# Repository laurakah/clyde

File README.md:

# Clyde

Clyde is an indoor room mapping roboter.

He is able to explore rooms, measure them and recognize them.

Clyde returns a map of the surveyed room to his user.

A possible field of use for Clyde could be the investigation of wireless signal quality on different spots in one or more rooms.

       .---.           _....._
     /  p  `\     .-""`:     :`"-.
     |__   - |  ,'     .     '    ',
      ._>    \ /:      :     ;      :,
       '-.    '\`.     .     :     '  \
          `.   | .'._.' '._.' '._.'.  |
            `;-\.   :     :     '   '/,__,
            .-'`'._ '     .     : _.'.__.'
           ((((-'/ `";--..:..--;"` \
               .'   /           \   \
              ((((-'           ((((-'

## directory structure

project/	– project documentation

software/	– software components for the robot (plus develepment tools)

hardware/	- hardware components for the robot

## system design

## build status for simulator tests

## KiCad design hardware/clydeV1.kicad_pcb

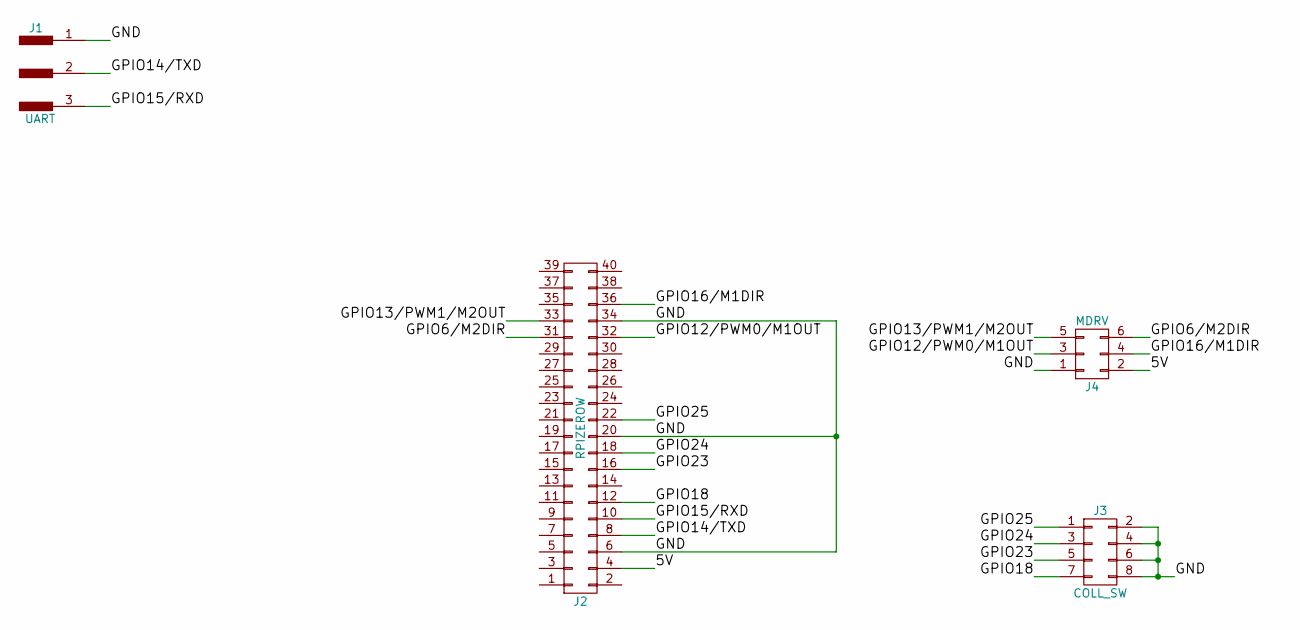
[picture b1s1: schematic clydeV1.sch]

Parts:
J1: UART; Pin_Header_Angled_1x03_Pitch2.54mm
J2: RPIZEROW; Socket_Strip_Straight_2x20_Pitch2.54mm
J3: COLL_SW; Pin_Header_Angled_2x04_Pitch2.54mm
J4: MDRV; Pin_Header_Angled_2x03_Pitch2.54mm

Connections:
/5V: J2.4, J4.2
/GND: J1.1, J2.6, J2.20, J2.34, J3.2, J3.4, J3.6, J3.8, J4.1
/GPIO6/M2DIR: J2.31, J4.6
/GPIO12/PWM0/M1OUT: J2.32, J4.3
/GPIO13/PWM1/M2OUT: J2.33, J4.5
/GPIO14/TXD: J1.2, J2.8
/GPIO15/RXD: J1.3, J2.10
/GPIO16/M1DIR: J2.36, J4.4
/GPIO18: J2.12, J3.7
/GPIO23: J2.16, J3.5
/GPIO24: J2.18, J3.3
/GPIO25: J2.22, J3.1

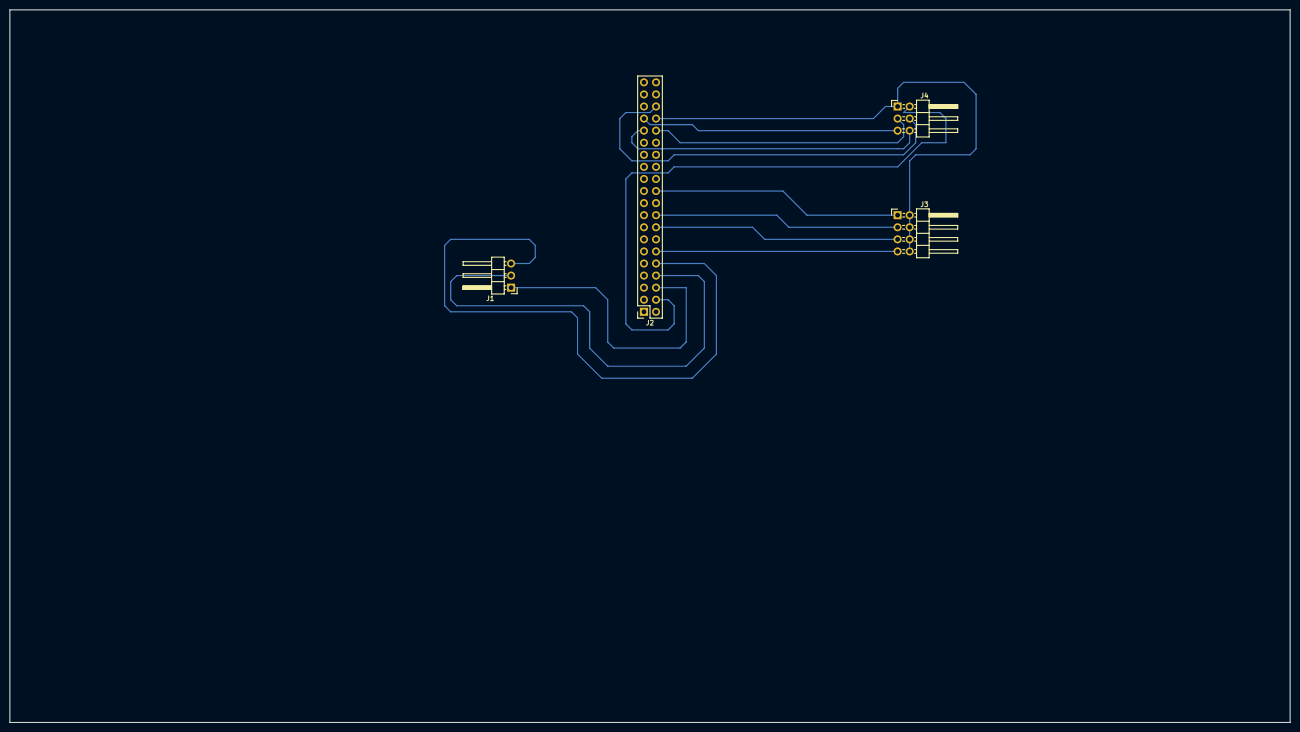
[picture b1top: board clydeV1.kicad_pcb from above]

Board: 2 copper layers, 269.2 x 149.9 mm, 4 parts (0 on the bottom side), 12 nets.

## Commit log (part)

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2017-07-16 update README.md - what is Clyde?
2017-07-16 add features.txt
2017-07-18 Components: Added links for sourcing components.
2017-07-18 Added images of our components.
2017-07-19 sim: Moved python code to sim directory.
2017-07-19 sim: Added Makefile to execute our tests.
2017-07-19 include build status for simulator tests in README.md
2017-07-19 SIM: add game map class + tests
2017-07-19 sim: Updated Makefile to execute gameMapTest.py as well.
2017-07-19 README: Use raw SVG for block diagram image.
2017-07-19 project: Generate .PNG output for block diagrams.
2017-07-19 README: Removed square braces not needed to display block diagram image.
2017-07-19 translate README.md and features.txt
2017-07-19 add features to README.md
2017-07-22 SIM: initial commit for simulator environment
2017-07-22 SIM: Added execution of simTest.py to Makefile.
2017-07-23 SIM: add time out and run wrapper + tests
2017-07-23 SIM: add baseRoomDetectionBrain + tests
2017-07-23 SIM: Added main.py to call simulator.
2017-07-23 SIM: Refactored main.py.
2017-07-23 SIM: add 4 new test maps
2017-07-23 SIM: Execute simulations for maps in order.
2017-07-23 SIM: WIP Added static method to GameMap to validate game map file lines.
2017-07-24 SIM: implement different exit codes for simulator
2017-07-24 SIM: Show exit code message in sim main() output.
2017-07-29 SIM: add collision detection on orientation up + tests
2017-07-29 SIM: clean up test code
2017-07-29 SIM: update player sim to give the right inputs and outputs to the brain sim
2017-07-29 SIM: exit with non-zero when sim execution failed.
2017-07-29 SIM: adjusted per-map result output format.
2017-07-30 SIM: add move function for player and player get position function
2017-07-30 SIM: Add function to return non-collision fields of a map.
2017-07-30 SIM: Added start position to report.
2017-07-30 SIM: Add more tests for getNonCollisionFields() to force our implementation to improve.
2017-07-30 SIM: add setPosition function for testing
2017-07-30 SIM: Added Sim.getStepDelay().
2017-07-30 SIM: Refactored Sim.step().
2017-07-30 SIM: Rename stepDelay to express the unit step delay represents (milliseconds).
2017-07-30 SIM: Pass delay to Sim in main.py. Updated usage/help.
2017-08-05 SIM: add getPlayerMap function in sim + tests
2017-08-05 SIM: add simMap and playerMap to report
2017-08-05 SIM: add random player start orientationon sim init
2017-08-06 SIM: normalize locations in game map array function + tests
2017-08-08 SIM: add follow function for player in draw function
2017-08-08 SIM: Add drawSimMap() with player position.
2017-08-08 SIM: Added new draw() that calls drawSimMap().
2017-08-08 SIM: Use class symbols for game map field values.
2017-08-10 SIM: clean up exceptions for base brain class
2017-08-10 SIM: add loadMapFile() to game map
2017-08-10 SIM: Add TODO and FIXME comments.
2017-08-12 SIM: Add code to draw() so sim and player map are displayed side by side.
2017-08-12 SIM: Made SimulatorLauncher test case class name reflect its purpose.
2017-08-12 SIM: Allow finding brain modules (via SimulatorLauncher).
2017-08-12 SIM: Rename method to get brain class names and change it to return class paths.
2017-08-12 SIM: Make main.py find brains on its own or allow passing one or more brains as arguments.
2017-08-12 SIM: implement movement functions in step function of brain
2017-08-12 SIM: check that arr is of type list for getLocationFromArray and setLocationInArray functions
2017-08-12 SIM: throw exceptions when index is out of range for getLocation and setLocation functions
2017-08-12 SIM: fix coordinate index in isCollision functions
2017-08-12 SIM: rename baseRoomDetectionBrain to baseBrain without deleting files
2017-08-12 SIM: prevent brain from moving as long as front collision is given
2017-08-12 SIM: Adjust output of sim.
2017-08-12 SIM: beautify draw game map tests
2017-08-12 SIM: Refactor Player.init slightly.
2017-08-12 SIM: Clean up Player.move().
2017-08-12 SIM: Added stub for DullBrain and its test case.
2017-08-12 SIM: Ignore DullBrain for execution with main.py
2017-08-12 SIM: Make Sim drawSimMap() and drawPlayerMap() draw player with orientation.
2017-08-12 SIM: Move loading class to main() of main.py.
2017-08-12 SIM: Have rv declared in main().
2017-08-12 SIM: Add comments to launchSim().
2017-08-13 SIM: make getSimMap() and getPlayerMap() return a gameMap object instead of an array
2017-08-13 SIM: Move parts of sim init into new reset() func.
2017-08-13 SIM: Refactor sim.init() into smaller parts.
2017-08-13 SIM: have dullBrain for testing purposes
2017-08-13 SIM: give simulator player.getOrientation() method
2017-08-13 SIM: give theaseus brain isFinished() method
2017-08-16 SIM: check that brain has map with start location and appends map according to orientation
2017-08-16 SIM: append brain map with collision and non collision fields for front collision
2017-08-16 SIM: Make launchSim() return dict (that is goint to be the report).
2017-08-16 SIM: Fixup for 2d375c3 - forgot to change order of arguments when calling launchSim).
2017-08-20 HARDWARE: add kicat project for circuit board
2017-08-20 SIM: rename game map objects from m to mObj
2017-08-20 SIM: give game map writeMapFile()
2017-08-20 SIM: Make launchSimForAllMaps() ignore maps passed using excludeMaps list argument.
2017-08-20 SIM: Verify launchSimForAllMaps() passes brainClassPath to launchSim().
2017-08-20 SIM: Verify launchSimForAllMaps() passes path to gameMapFile to launchSim().
2017-08-20 SIM: Verify timeout gets passed from launchSimForAllMaps() to launchSim().
2017-08-20 SIM: Verify follow arg is passed from launchSimForAllMaps() to launchSim().
2017-08-20 SIM: Make fakeLaunchSim() more compact.
2017-08-20 SIM: Clean up launchSimForAllMaps() tests.
2017-08-22 SIM: store last orientation on collision
2017-08-22 SIM: add getNextOrientation(), fixes #15
2017-08-22 SIM: refactor getNextOrientation()
2017-08-22 SIM: Replace launchSimForAllMaps() with TDD version from simLauncher.
2017-08-23 SIM: Replaced call to player.getOrientation() with self.getOrientation() in sim.
2017-08-23 SIM: replace orientation value with global brain symbols
2017-08-23 SIM: Make GameMap.arrayToText() optionally pad short lines of text maps.
2017-08-23 SIM: clean up comments
2017-08-26 SIM: Added comments to step() inside theseus brain.
2017-08-26 SIM: Move getting location value inside theseusBrain.step() to one place.
2017-08-26 SIM: add function to expand game map vertically
2017-08-26 SIM: add expandGameMap function, fixes #10
2017-08-26 SIM: refactor player move() to call getNextPosition()
2017-08-27 SIM: expand step function to prepend map on orientation down and left
2017-08-27 SIM: make sure getNextPosition is only called when no collision
2017-08-27 SIM: remove debugging code
2017-08-27 SIM: translate unknown fields into ? in string, fixes #20
2017-08-27 SIM: FIX: make sure y prepend operations expand x too
2017-08-27 SIM: Make maps be executed in order. fixes #18.
2017-08-27 SIM: raise exception when None is passed to getNextPosition(), fixes #23
2017-08-27 SIM: move update map stuff to own function
2017-08-27 SIM: Slightly refactor launchSim() in main.py so we can replace it without losing status output features.
2017-08-27 SIM: refactor updateMap()
2017-08-27 SIM: FIX: only increment position on orientation left and down when not prepending
2017-08-27 SIM: FIX: make withinMap() return false when called with zero
2017-08-30 SIM: refactor coordinates everywhere to use Coordinate class
2017-08-30 SIM: rename simple brain class
2017-09-02 SIM: Use new Coordinate object in main.py.
2017-09-02 SIM: add getLastPosition()
2017-09-02 SIM: add step log for brains
2017-09-03 SIM: add function to set up mocks and refactor tests for simple brain
2017-09-03 SIM: refactor last two functions in simple brain to use fake mocks
2017-09-03 SIM: Make launchSimForAllMaps() pass 'position' string to launchSim().
2017-09-03 SIM: Make launchSimForAllMaps() pass 'orientation' string to launchSim().
2017-09-03 SIM: make sure, getBrainMap() from baseBrain returns copy
2017-09-03 SIM: Fixup for passing position and orientation (but now in actual main.py).
2017-09-03 SIM: Added todo comments to simLauncherTest.
2017-09-03 SIM: Handle KeyboardInterrupt in main.py, fixes #22
2017-09-03 SIM: remove FIXME for getNonCollisionFields()
2017-09-03 SIM: remove pos, ori and direction from move helper function
2017-09-03 SIM: Added sparator comments between Sim unit tests.
2017-09-06 SIM: use fake values in every player isFinished test
2017-09-06 SIM: Fixed typo in comment.
2017-09-06 SIM: Simplify actual padding of map text.
2017-09-06 SIM: revert changes on test for player isFinished()
2017-09-06 SIM: Have GameMap.toText() that calls static arrayToText().
2017-09-06 SIM: Use GameMap.toText() where there is very low chance of breaking something.
2017-09-06 SIM: Have test that Sim.drawSimMap() calls toText() with pad=True.
2017-09-06 SIM: Removed outdated fixme comment.
2017-09-06 SIM: Adjusted test name for where we test Sim.draw() passes pad=True to toText().
2017-09-06 SIM: Fix malfunctioning sim.draw() where player map not properly displayed.
    The problem was that the player map (on the right side), actually the last
    line of the map, was moved towards the left into the sim map. This was because
    we used rstrip() on the text of the sim map (with the intention of removing the
    last new-line character. But, we forgot to pass "\n" to rstrip, which in turn
    removed all the spaces that have been added by GameMap.toText(pad=True) before.
    Hence, padding was working but destroyed by Sim.draw().
2017-09-15 SIM: Added new static method to find map files in a directory.
2017-09-15 SIM: Adjusted launchSimForAllMaps() to use list of maps rather than map file directory.
2017-09-15 SIM: Make launchSimForAllMaps() no longer filter maps by startsWith string.
2017-09-15 SIM: Make sure brain and map dir are used when alternative paths are supplied as command-line arguments.
2017-09-15 SIM: Have launchSimForAllBrains().
2017-09-15 SIM: Slightly simplify validity checking of position and orientation in simLauncher.
2017-09-15 SIM: Add array of orientation strings to base brain.
2017-09-16 SIM: Have local vars for default command-line option values.
2017-09-16 SIM: Have short-hand name for simLauncher class in main.py.
2017-09-16 SIM: Have functions to transform position and orientation strings to values.
2017-09-16 SIM: Allow loadig brains and maps from alternative directories.
2017-09-16 SIM: Use __str__ of Coordinate when printing X/Y values.
2017-09-16 SIM: Fixed line endings for some error and status messages.
2017-09-16 SIM: fix setting location value at own position bug
2017-09-16 SIM: temporary fix: make sim draw player start position
2017-09-16 SIM: Add factory to create coord from string.
2017-09-17 SIM: Use class symbols for orientation.
2017-09-17 SIM: translate start position when prepending brain map
2017-09-17 SIM: Use class symbol for brain class file 'ends with' string.
2017-09-17 SIM: Fix sim.run() to call draw only as long as running state is true (number of calls to draw equals number of steps).
2017-09-17 SIM: have field to store brains first collision position
2017-09-17 SIM: Add _STR to end of player position symbol names.
2017-09-17 SIM: Have array of player position values in game map.
2017-09-23 SIM: Added test for Player.getPosition().
2017-09-23 SIM: make theseus brain ask for side and back collision inputs, fixes #9
2017-09-23 SIM: give player side and back collisions
2017-09-23 SIM: remove unused createBlankMap() function
2017-09-23 SIM: comment position and indentation
2017-09-24 SIM: Added comments to sim test.
2017-09-24 SIM: add required code from simple brain to theseus brain, fixes #61
2017-09-24 SIM: fix minor differences in formatting between simple and theseus brain
2017-09-24 SIM: Use unittest discover module to find unit tests and execute them.
2017-09-24 TB: fix spinning when no collision bug
2017-10-26 HARDWARE: update circuit diagram
2017-10-27 PROJECT: Add TI DRV8801 motor driver datasheet.
2017-10-28 PI: Parameterize PWM script.
2019-12-11 Jenkinsfile: Use common notification code.
